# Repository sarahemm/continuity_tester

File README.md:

# continuity_tester
Continuity Tester design, optimized for reverse engineering PCBs

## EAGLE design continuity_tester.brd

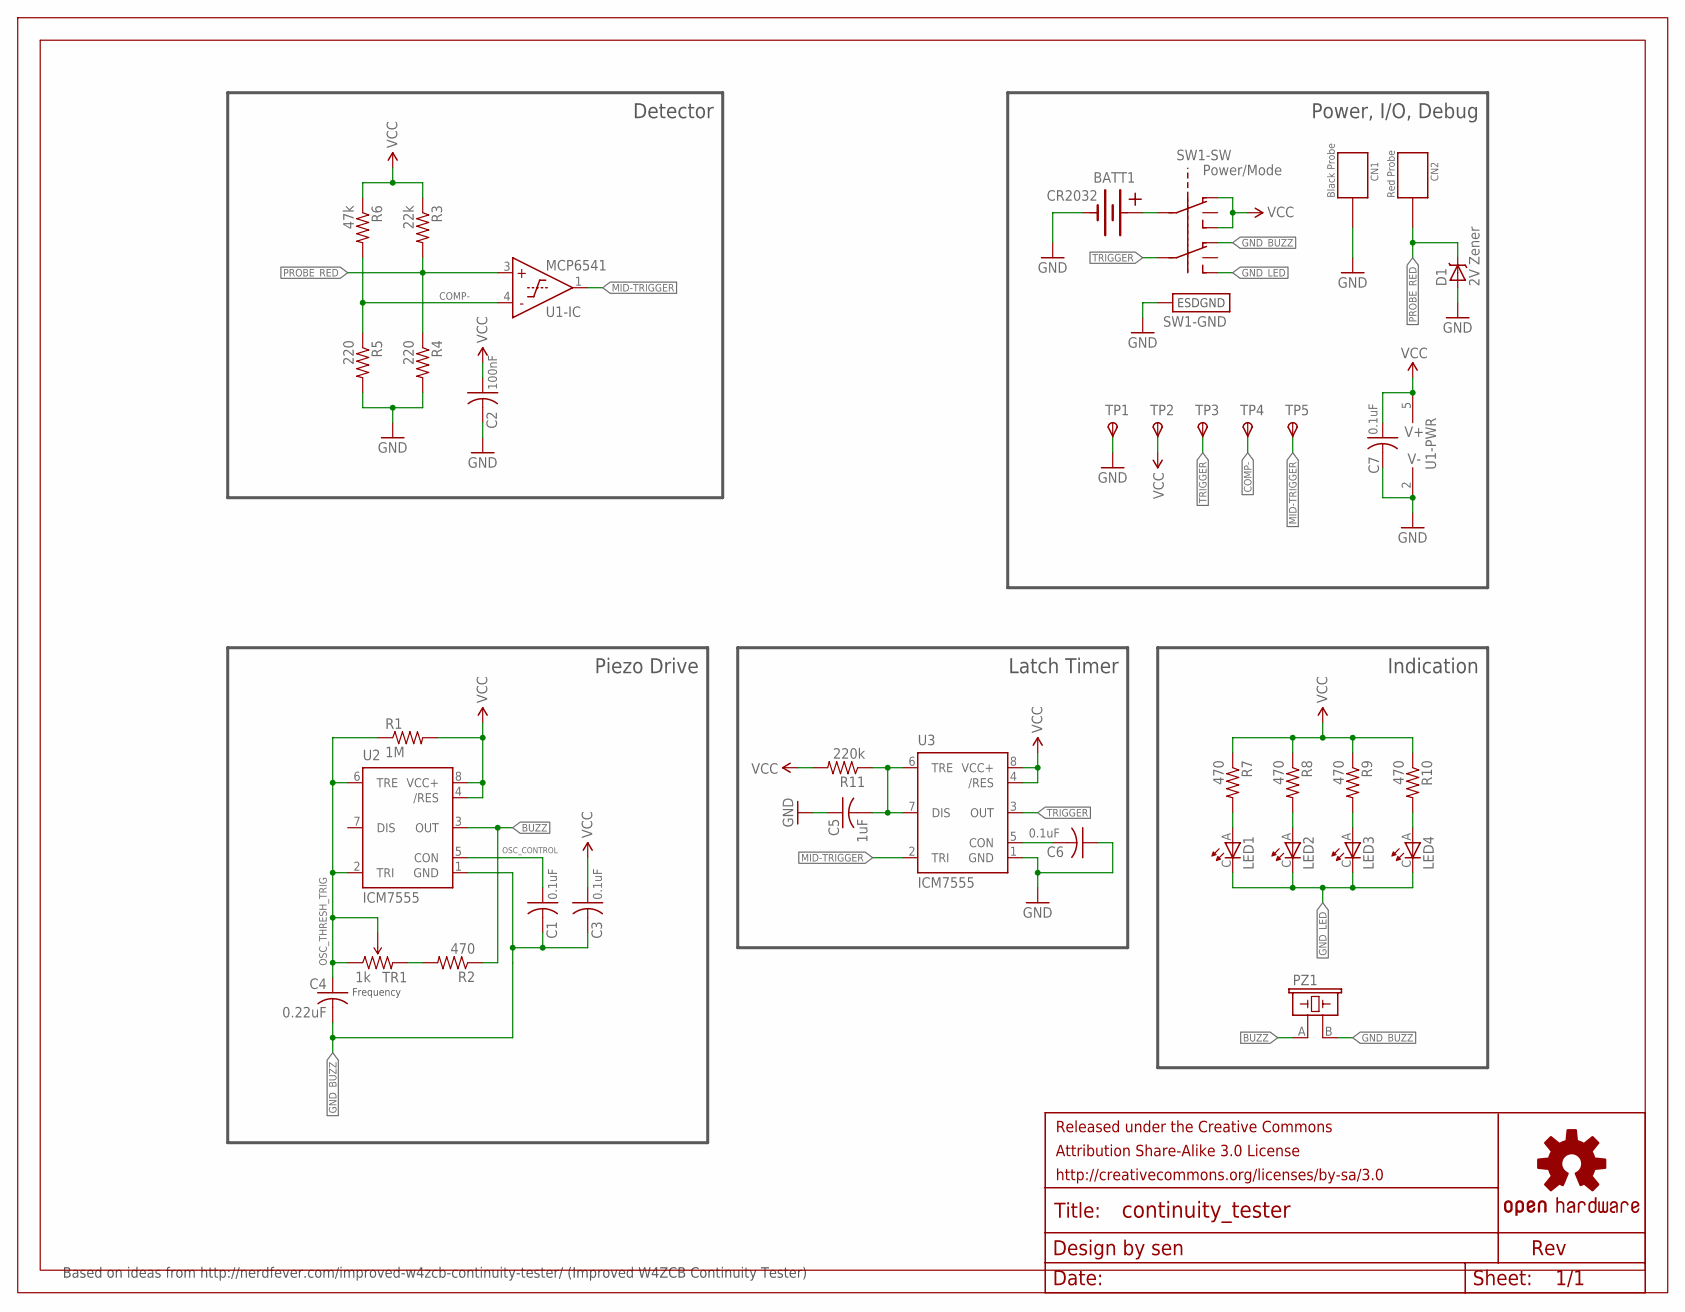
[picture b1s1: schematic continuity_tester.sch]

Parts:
BATT1: CR2032; BK-912-CR2032
C1, C3, C6, C7: 0.1uF; C0603
C2: 100nF; C0603
C4: 0.22uF; C0603
C5: 1uF; C0603
CN1: Black Probe; CALTEST-CT3151
CN2: Red Probe; CALTEST-CT3151
D1: 2V Zener; DO-219AC
FRAME1: FRAME-LETTER-GRID-OSHW-SENOSHW-LOGO-L; OSHW-LOGO-L
LED1, LED2, LED3, LED4: LITEON-LTST020
PZ1: MURATA-PKMCS0909
R1: 1M; R0603
R2, R7, R8, R9, R10: 470; R0603
R3: 22k; R0603
R4, R5: 220; R0603
R6: 47k; R0603
R11: 220k; R0603
SW1: Power/Mode; ESWITCH-EG2308
TP1: GND; B1,27
TP2: VCC; B1,27
TP3: TRIGGER; B1,27
TP4: COMP-; B1,27
TP5: MID-TRIGGER; B1,27
TR1: 1k; NIDEC-ST4EA
U1: MCP6541; SOT23-5
U2, U3: ICM7555; SO08

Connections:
BUZZ: PZ1.A (1), R2.1, U2.3 (OUT)
COMP-: R5.1, R6.2, TP4.TP, U1.4 (IN-)
GND: BATT1.- (-1), C2.2, C5.1, C6.1, C7.2, CN1.A, CN1.B, CN1.C, CN1.D, D1.A, R4.2, R5.2, SW1.SUPPORT1 (ESDGND), SW1.SUPPORT2 (ESDGND), TP1.TP, U1.2 (V-), U3.1 (GND)
GND_BUZZ: C1.2, C3.2, C4.2, PZ1.B (2), SW1.5 (2A), U2.1 (GND)
GND_LED: LED1.C, LED2.C, LED3.C, LED4.C, SW1.8 (2C)
LED1_R: LED1.A, R7.2
LED2_R: LED2.A, R8.2
LED3_R: LED3.A, R9.2
LED4_R: LED4.A, R10.2
MID-TRIGGER: TP5.TP, U1.1 (OUT), U3.2 (TRI)
OSC_CONTROL: C1.1, U2.5 (CON)
OSC_THRESH_TRIG: C4.1, R1.1, TR1.CCW, TR1.WIPER, U2.2 (TRI), U2.6 (TRE)
PROBE_RED: CN2.A, CN2.B, CN2.C, CN2.D, D1.K (C), R3.2, R4.1, U1.3 (IN+)
TR1_R2: R2.2, TR1.CW
TRIGGER: SW1.7 (2), TP3.TP, U3.3 (OUT)
U3-CON: C6.2, U3.5 (CON)
U3-TREDIS: C5.2, R11.1, U3.6 (TRE), U3.7 (DIS)
VCC: C2.1, C3.1, C7.1, R1.2, R3.1, R6.1, R7.1, R8.1, R9.1, R10.1, R11.2, SW1.1 (1A), SW1.4 (1C), TP2.TP, U1.5 (V+), U2.4 (/RES), U2.8 (VCC+), U3.4 (/RES), U3.8 (VCC+)
VCC_PRESWITCH: BATT1.+1 (+2), SW1.3 (1)

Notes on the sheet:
Frequency
Indication
Piezo Drive
Detector
Power, I/O, Debug
Based on ideas from http://nerdfever.com/improved-w4zcb-continuity-tester/ (Improved W4ZCB Continuity Tester)
Latch Timer

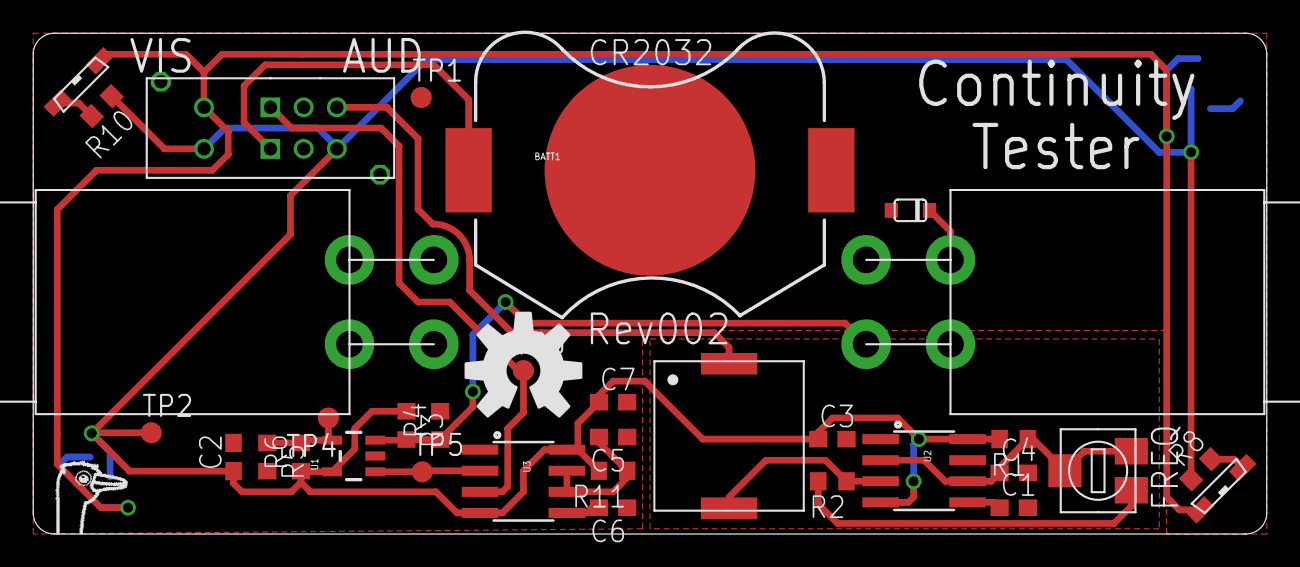
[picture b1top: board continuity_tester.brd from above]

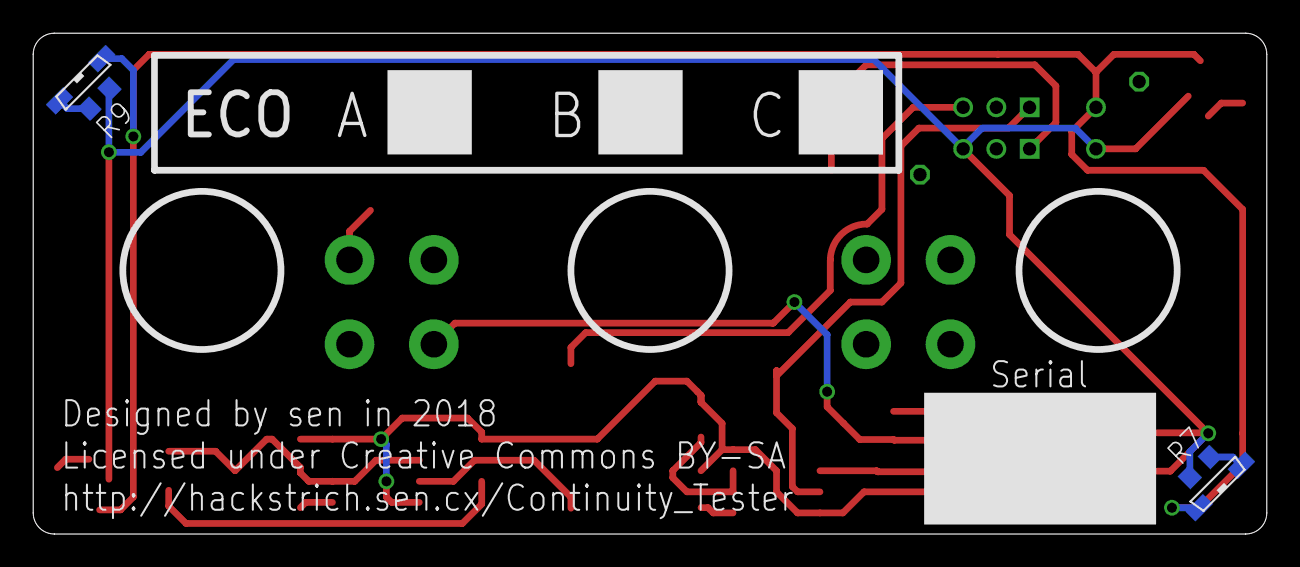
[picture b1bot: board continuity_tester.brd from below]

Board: 2 copper layers, 74.3 x 30.2 mm, 39 parts (4 on the bottom side), 19 nets.

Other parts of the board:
U$1: STRICH-LOGO-R

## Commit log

2017-12-12 Adding complete/checklisted schematic.
2017-12-12 Board routing in progress.
2017-12-13 Board routed and checklisted, ready for CAM.
2017-12-13 Adding complete CAM files, ready to send for manufacturing.
2018-01-16 Started making Rev002 updates to schematic. Not currently in a usable state!
2018-01-16 More improvements for Rev002 in progress.
    Extra 555 for latch timer in place.
    Replaced comparator w/ a push/pull one needed for latch, also uses 1/165th of the power of the old one.
    Replaced switch with one that's more appropriate and 1/5 the cost of the old one.
2018-01-16 Rev002 schematic complete.
2018-01-16 Checklist for Rev002 schematic completed.
2018-01-18 Rev002 board layout electrically complete, still need to finish silkscreen and check it.
2018-01-26 Completed and checklisted Rev002 schematic and board.
2018-01-26 Rev002 CAM files generated and checklisted.
2018-01-26 Updated BOM for Rev002 and removed unneeded fields.

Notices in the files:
continuity_tester.brd:
Licensed under Creative Commons BY-SA
parts and their libraries:
SparkFun-AnalogIC: Licensing:Creative Commons ShareAlike 4.0 International - https://creativecommons.org/licenses/by-sa/4.0
logos-sen: Released under the Creative Commons Attribution Share-Alike 3.0 License
logos-sen: http://creativecommons.org/licenses/by-sa/3.0
